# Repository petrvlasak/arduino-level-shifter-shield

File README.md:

# Arduino Logic Level Shifter Shield

This shield is used to convert the logic 1 (HIGH) voltage at the Arduino digital pins so that logic circuits that use a different logic 1 (HIGH) voltage can be connected to it. The Shield can be used with the Arduino UNO board and any other board that has the same layout and pinout as this board. The pins are divided into three groups of eight. It is possible to choose a different voltage for each of these three groups. In the third group, only four pins are connected to the Arduino. The remaining four pins S0 - S3 are of general use and convert the IOREF voltage to the voltage set for the third group. The voltage is changed by a switch that has three options:

1. Voltage 3.3 V from Arduino
2. The voltage set by the potentiometer on the regulator varies between approximately 1.5 V - 2.8 V (the input for the regulator can be pin +5V or pin Vin)
3. External voltage - The allowed range of this voltage is 1.4V - 3.6V

## Schematic

## Manufacturing

The PCB manufacturing files are located [here](/manufacturing/).

## Placement plan

## Bill of materials

| Reference | Quantity | Value | Description |
| --- | --- | --- | --- |
| C11, C14, C15, C21, C24, C25, C31, C34, C35 | 9 | 100n | Capacitor SMD 0805 |
| C12, C22, C32 | 3 | 1u | Capacitor SMD 0805 |
| C13, C23, C33 | 3 | 100u | Capacitor THT Radial D6.3mm P2.50mm |
| R11, R21, R31 | 3 | 1k | Resistor SMD 0603 |
| R12, R22, R32 | 3 | 1k | Potentiometer Bourns 3362P Vertical |
| R13, R23, R33 | 3 | 200 | Resistor SMD 0603 |
| R14, R24, R34 | 3 | 10k | Resistor SMD 0603 |
| U11, U21, U31 | 3 |  | LM317 TO-252 |
| U12, U22, U32 | 3 |  | TXS0108EPW |
| SW1, SW2, SW3 | 3 |  | OS103011MA7QP1 |
| J47, J54, J55 | 3 |  | Pin Header 1x3 2.54mm |
| J3 | 1 |  | Pin Socket 1x3 2.54mm |
| J1, J2, J51, J52 | 4 |  | Pin Socket 1x5 2.54mm |
| J56 | 1 |  | Pin Socket 1x8 2.54mm |
| J53 | 1 |  | Pin Socket 1x10 2.54mm |

Components J41, J42, J43, J44, J45 and J46 are special pin headers for Arduino shields. I found two ways to buy them:

1. From SparkFun: 1 x [Arduino Stackable Header Kit - R3](https://www.sparkfun.com/products/11417) and 2 x [Stackable Header - 3 Pin (Female, 0.1")](https://www.sparkfun.com/products/13875)
2. From Adafruit: 1 x [Shield stacking headers for Arduino (R3 Compatible)](https://www.adafruit.com/product/85)

And finally you need one Mini Jumper 1x2 2.54mm to configure the input for the regulators (+5V or Vin).

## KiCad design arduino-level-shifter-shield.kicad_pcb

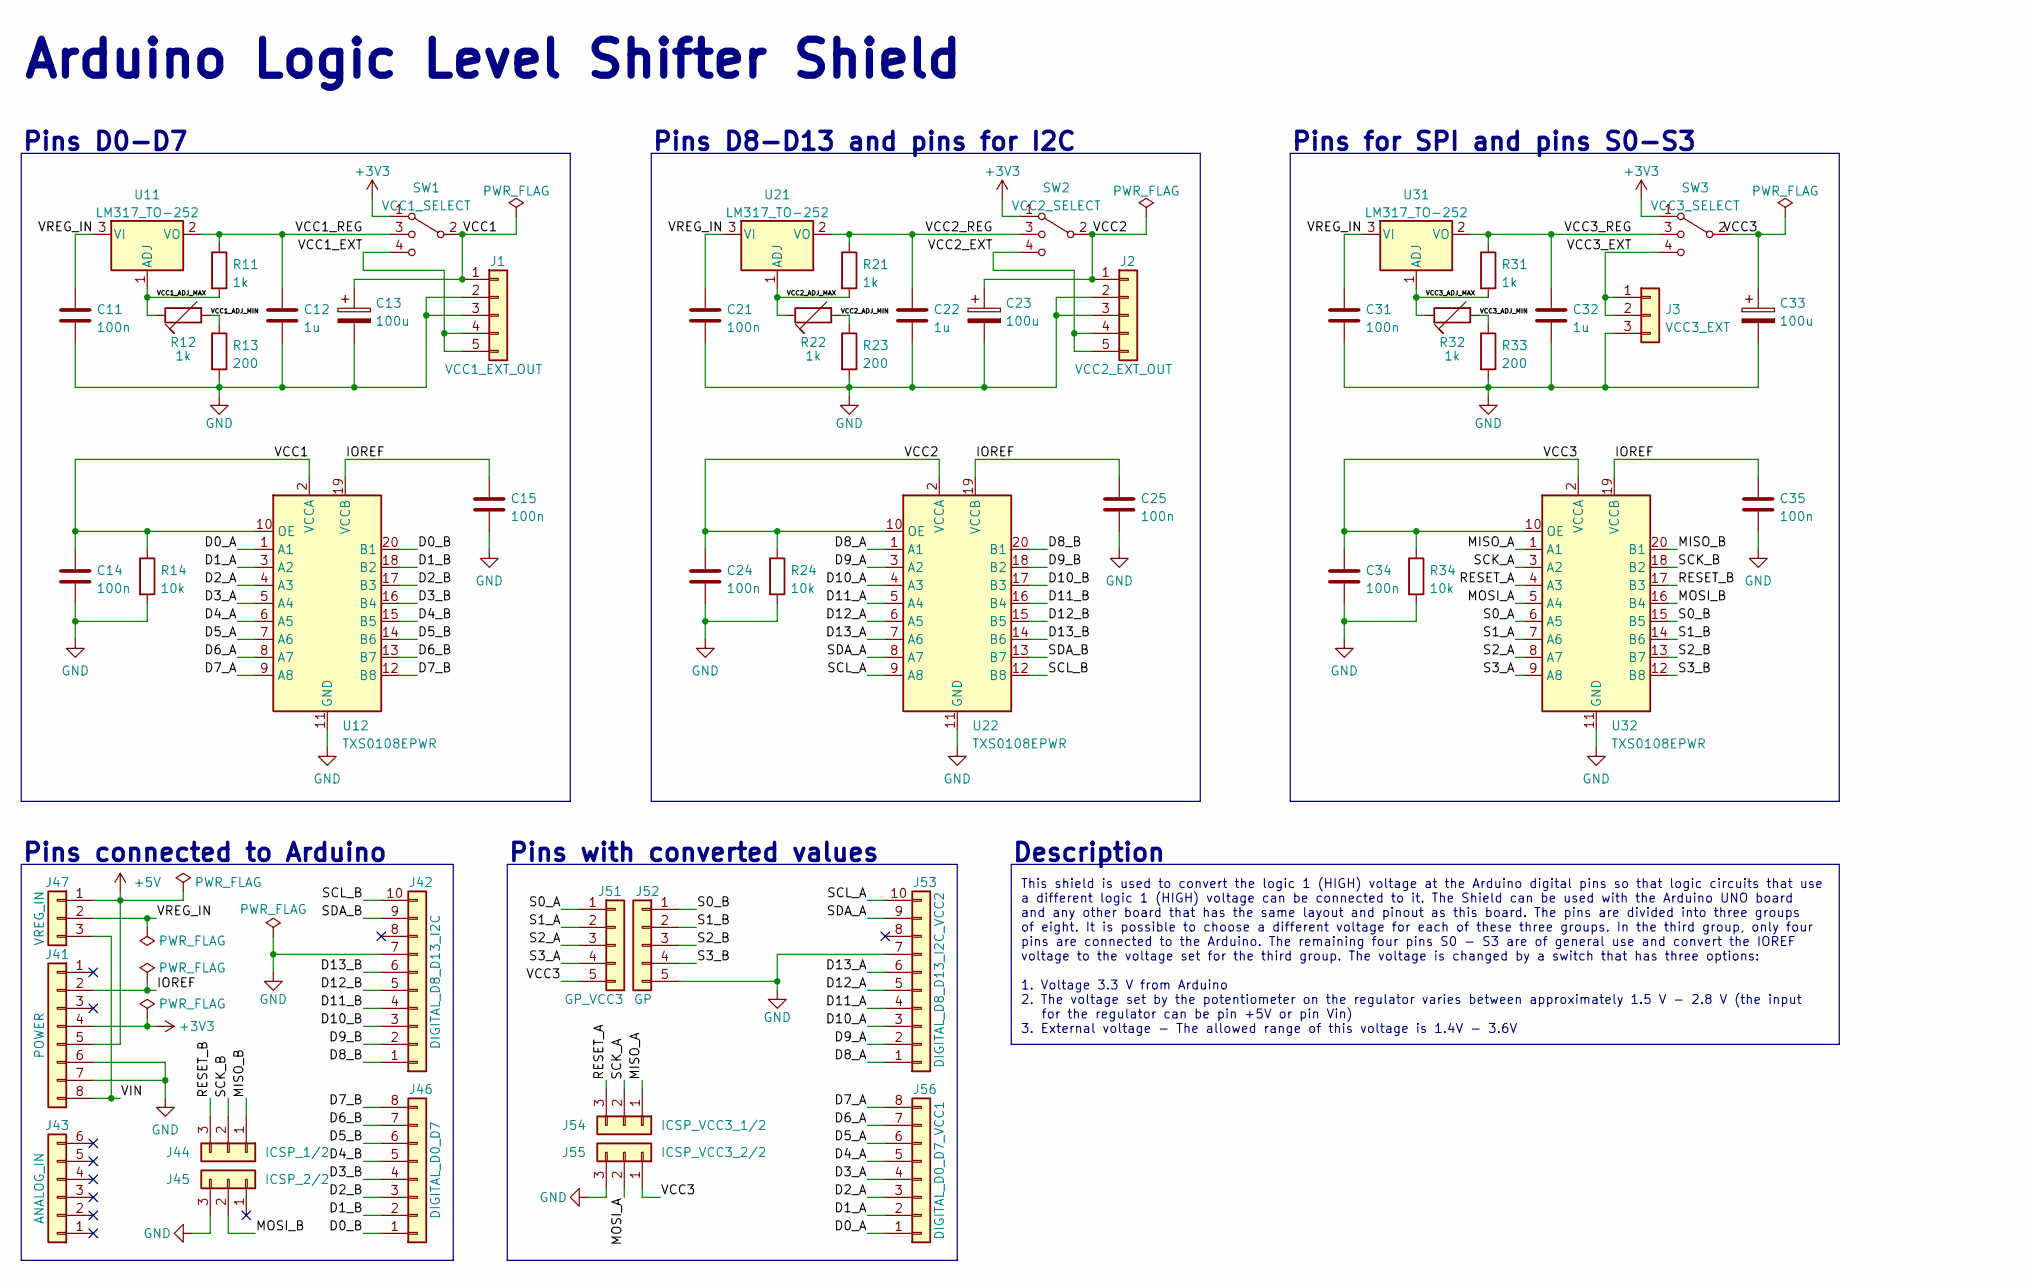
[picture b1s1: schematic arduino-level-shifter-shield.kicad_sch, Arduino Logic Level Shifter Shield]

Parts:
C11, C14, C15, C21, C24, C25, C31, C34, C35: 100n; C_0805_2012Metric
C12, C22, C32: 1u; C_0805_2012Metric
C13, C23, C33: 100u; CP_Radial_D6.3mm_P2.50mm
J1: VCC1_EXT_OUT; PinSocket_1x05
J2: VCC2_EXT_OUT; PinSocket_1x05
J3: VCC3_EXT; PinSocket_1x03
J41: POWER; PinSocket_1x08_long_legs
J42: DIGITAL_D8_D13_I2C; PinSocket_1x10_long_legs
J43: ANALOG_IN; PinSocket_1x06_long_legs
J44: ICSP_1/2; PinSocket_1x03_long_legs
J45: ICSP_2/2; PinSocket_1x03_long_legs
J46: DIGITAL_D0_D7; PinSocket_1x08_long_legs
J47: VREG_IN; PinHeader_1x03
J51: GP_VCC3; PinSocket_1x05
J52: GP; PinSocket_1x05
J53: DIGITAL_D8_D13_I2C_VCC2; PinSocket_1x10
J54: ICSP_VCC3_1/2; PinHeader_1x03
J55: ICSP_VCC3_2/2; PinHeader_1x03
J56: DIGITAL_D0_D7_VCC1; PinSocket_1x08
R11, R21, R31: 1k; R_0603_1608Metric
R12, R22, R32: 1k; Potentiometer_Bourns_3362P_Vertical
R13, R23, R33: 200; R_0603_1608Metric
R14, R24, R34: 10k; R_0603_1608Metric
SW1: VCC1_SELECT; SW_CuK_OS103011MA7QP1_SP3T_Angled
SW2: VCC2_SELECT; SW_CuK_OS103011MA7QP1_SP3T_Angled
SW3: VCC3_SELECT; SW_CuK_OS103011MA7QP1_SP3T_Angled
U11, U21, U31: LM317_TO-252; TO-252-2
U12, U22, U32: TXS0108EPWR; TSSOP-20_4.4x6.5mm_P0.65mm

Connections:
+3V3: J41.4, SW1.1, SW2.1, SW3.1
+5V: J41.5, J47.1
/D0_A: J56.1, U12.1 (A1)
/D0_B: J46.1, U12.20 (B1)
/D1_A: J56.2, U12.3 (A2)
/D1_B: J46.2, U12.18 (B2)
/D2_A: J56.3, U12.4 (A3)
/D2_B: J46.3, U12.17 (B3)
/D3_A: J56.4, U12.5 (A4)
/D3_B: J46.4, U12.16 (B4)
/D4_A: J56.5, U12.6 (A5)
/D4_B: J46.5, U12.15 (B5)
/D5_A: J56.6, U12.7 (A6)
/D5_B: J46.6, U12.14 (B6)
/D6_A: J56.7, U12.8 (A7)
/D6_B: J46.7, U12.13 (B7)
/D7_A: J56.8, U12.9 (A8)
/D7_B: J46.8, U12.12 (B8)
/D8_A: J53.1, U22.1 (A1)
/D8_B: J42.1, U22.20 (B1)
/D9_A: J53.2, U22.3 (A2)
/D9_B: J42.2, U22.18 (B2)
/D10_A: J53.3, U22.4 (A3)
/D10_B: J42.3, U22.17 (B3)
/D11_A: J53.4, U22.5 (A4)
/D11_B: J42.4, U22.16 (B4)
/D12_A: J53.5, U22.6 (A5)
/D12_B: J42.5, U22.15 (B5)
/D13_A: J53.6, U22.7 (A6)
/D13_B: J42.6, U22.14 (B6)
/IOREF: C15.1, C25.1, C35.1, J41.2, U12.19 (VCCB), U22.19 (VCCB), U32.19 (VCCB)
/MISO_A: J54.1, U32.1 (A1)
/MISO_B: J44.1, U32.20 (B1)
/MOSI_A: J55.2, U32.5 (A4)
/MOSI_B: J45.2, U32.16 (B4)
/RESET_A: J54.3, U32.4 (A3)
/RESET_B: J44.3, U32.17 (B3)
/S0_A: J51.1, U32.6 (A5)
/S0_B: J52.1, U32.15 (B5)
/S1_A: J51.2, U32.7 (A6)
/S1_B: J52.2, U32.14 (B6)
/S2_A: J51.3, U32.8 (A7)
/S2_B: J52.3, U32.13 (B7)
/S3_A: J51.4, U32.9 (A8)
/S3_B: J52.4, U32.12 (B8)
/SCK_A: J54.2, U32.3 (A2)
/SCK_B: J44.2, U32.18 (B2)
/SCL_A: J53.10, U22.9 (A8)
/SCL_B: J42.10, U22.12 (B8)
/SDA_A: J53.9, U22.8 (A7)
/SDA_B: J42.9, U22.13 (B7)
/VCC1: C13.1, C14.1, J1.1, R14.1, SW1.2, U12.2 (VCCA), U12.10 (OE)
/VCC1_ADJ_MAX: R11.2, R12.1, U11.1 (ADJ)
/VCC1_ADJ_MIN: R12.2, R13.1
/VCC1_EXT: J1.4, J1.5, SW1.4
/VCC1_REG: C12.1, R11.1, SW1.3, U11.2 (VO)
/VCC2: C23.1, C24.1, J2.1, R24.1, SW2.2, U22.2 (VCCA), U22.10 (OE)
/VCC2_ADJ_MAX: R21.2, R22.1, U21.1 (ADJ)
/VCC2_ADJ_MIN: R22.2, R23.1
/VCC2_EXT: J2.4, J2.5, SW2.4
/VCC2_REG: C22.1, R21.1, SW2.3, U21.2 (VO)
/VCC3: C33.1, C34.1, J51.5, J55.1, R34.1, SW3.2, U32.2 (VCCA), U32.10 (OE)
/VCC3_ADJ_MAX: R31.2, R32.1, U31.1 (ADJ)
/VCC3_ADJ_MIN: R32.2, R33.1
/VCC3_EXT: J3.1, J3.2, SW3.4
/VCC3_REG: C32.1, R31.1, SW3.3, U31.2 (VO)
/VIN: J41.8, J47.3
/VREG_IN: C11.1, C21.1, C31.1, J47.2, U11.3 (VI), U21.3 (VI), U31.3 (VI)
GND: C11.2, C12.2, C13.2, C14.2, C15.2, C21.2, C22.2, C23.2, C24.2, C25.2, C31.2, C32.2, C33.2, C34.2, C35.2, J1.2, J1.3, J2.2, J2.3, J3.3, J41.6, J41.7, J42.7, J45.3, J52.5, J53.7, J55.3, R13.2, R14.2, R23.2, R24.2, R33.2, R34.2, U12.11 (GND), U22.11 (GND), U32.11 (GND)

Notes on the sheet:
Pins for SPI and pins S0-S3
Pins with converted values
Pins D8-D13 and pins for I2C
Pins D0-D7
Arduino Logic Level Shifter Shield
This shield is used to convert the logic 1 (HIGH) voltage at the Arduino digital pins so that logic circuits that use a different logic 1 (HIGH) voltage can be connected to it. The Shield can be used with the Arduino UNO board and any other board that has the same layout and pinout as this board. T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
Pins connected to Arduino
Description

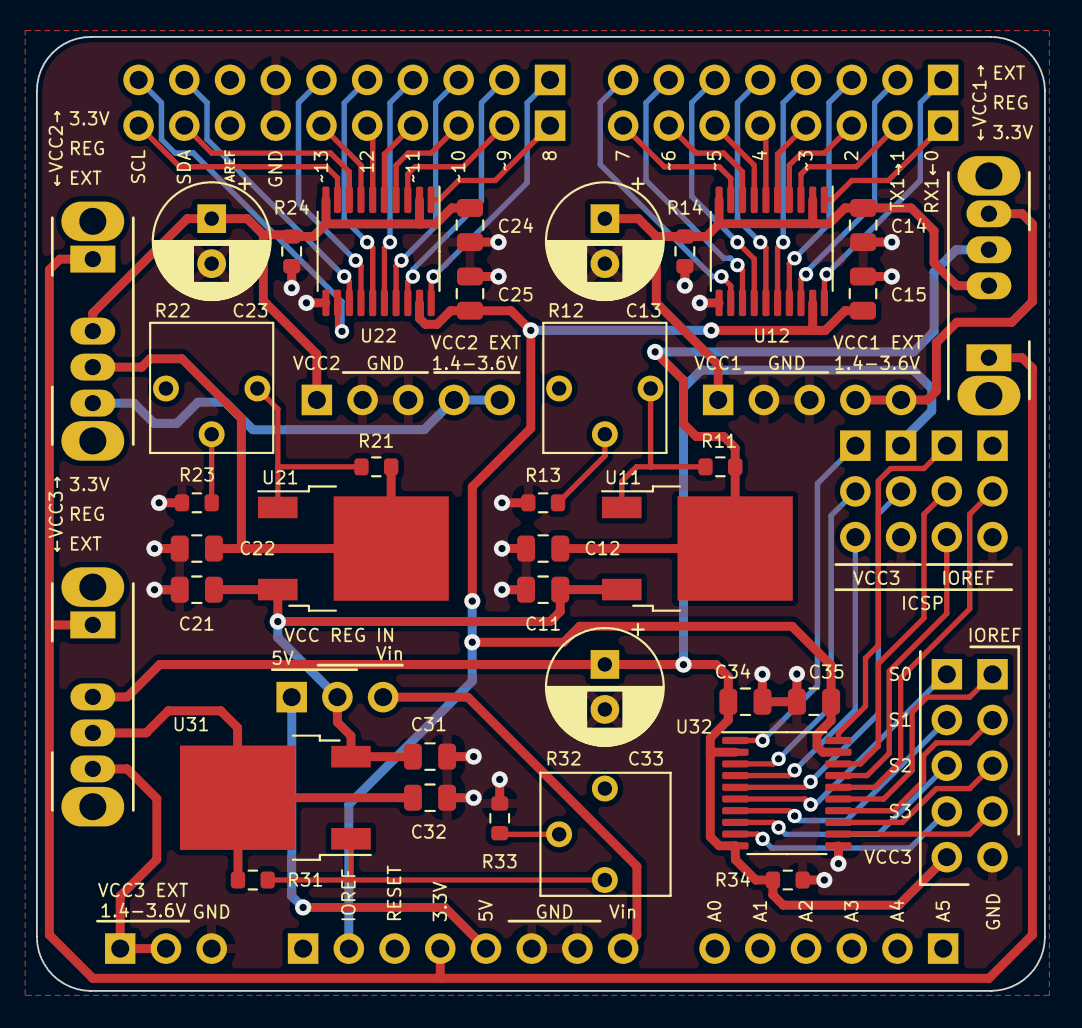
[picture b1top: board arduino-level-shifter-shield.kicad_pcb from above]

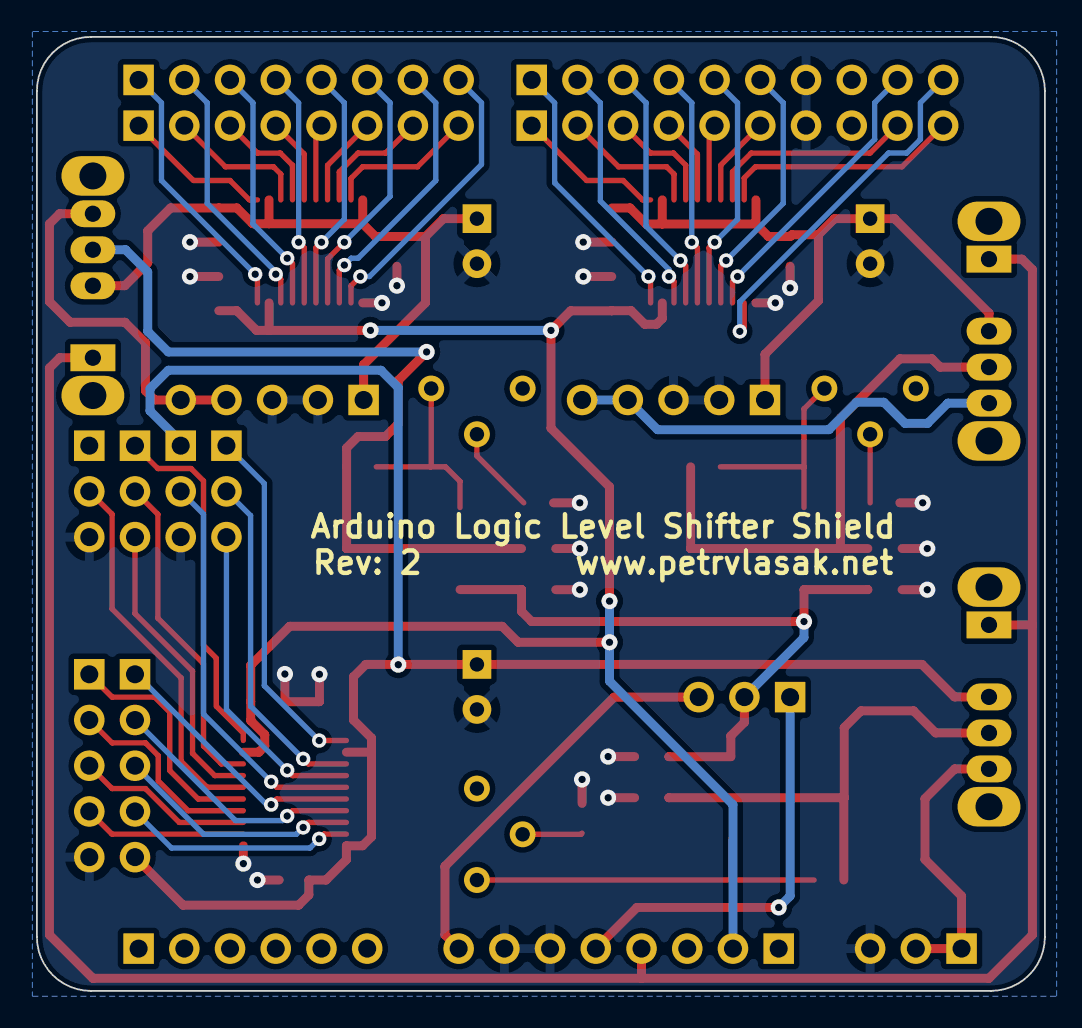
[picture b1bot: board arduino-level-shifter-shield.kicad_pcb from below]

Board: 2 copper layers, 56.0 x 53.0 mm, 52 parts (2 on the bottom side), 69 nets.

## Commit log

2023-03-20 Added license information
2023-04-16 Rev: 2

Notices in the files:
arduino-level-shifter-shield.kicad_pcb:
https://creativecommons.org/licenses/by-sa/4.0
License: CC BY-SA 4.0
